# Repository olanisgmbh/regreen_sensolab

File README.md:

# SensoLAB - make, learn and share

The vision of this project is to implement an universal platform which can be used as a citizen science tool and an interdisciplinary tool for schools.

#### the tools You need:

+ screwdrivers
+ solderstation
+ circle cutter
+ punching iron ( 3mm, 8mm )
+ a dremel milling/drilling tool
+ hammer

# Author
Norman Rembarz <norman.rembarz@olanis.de>

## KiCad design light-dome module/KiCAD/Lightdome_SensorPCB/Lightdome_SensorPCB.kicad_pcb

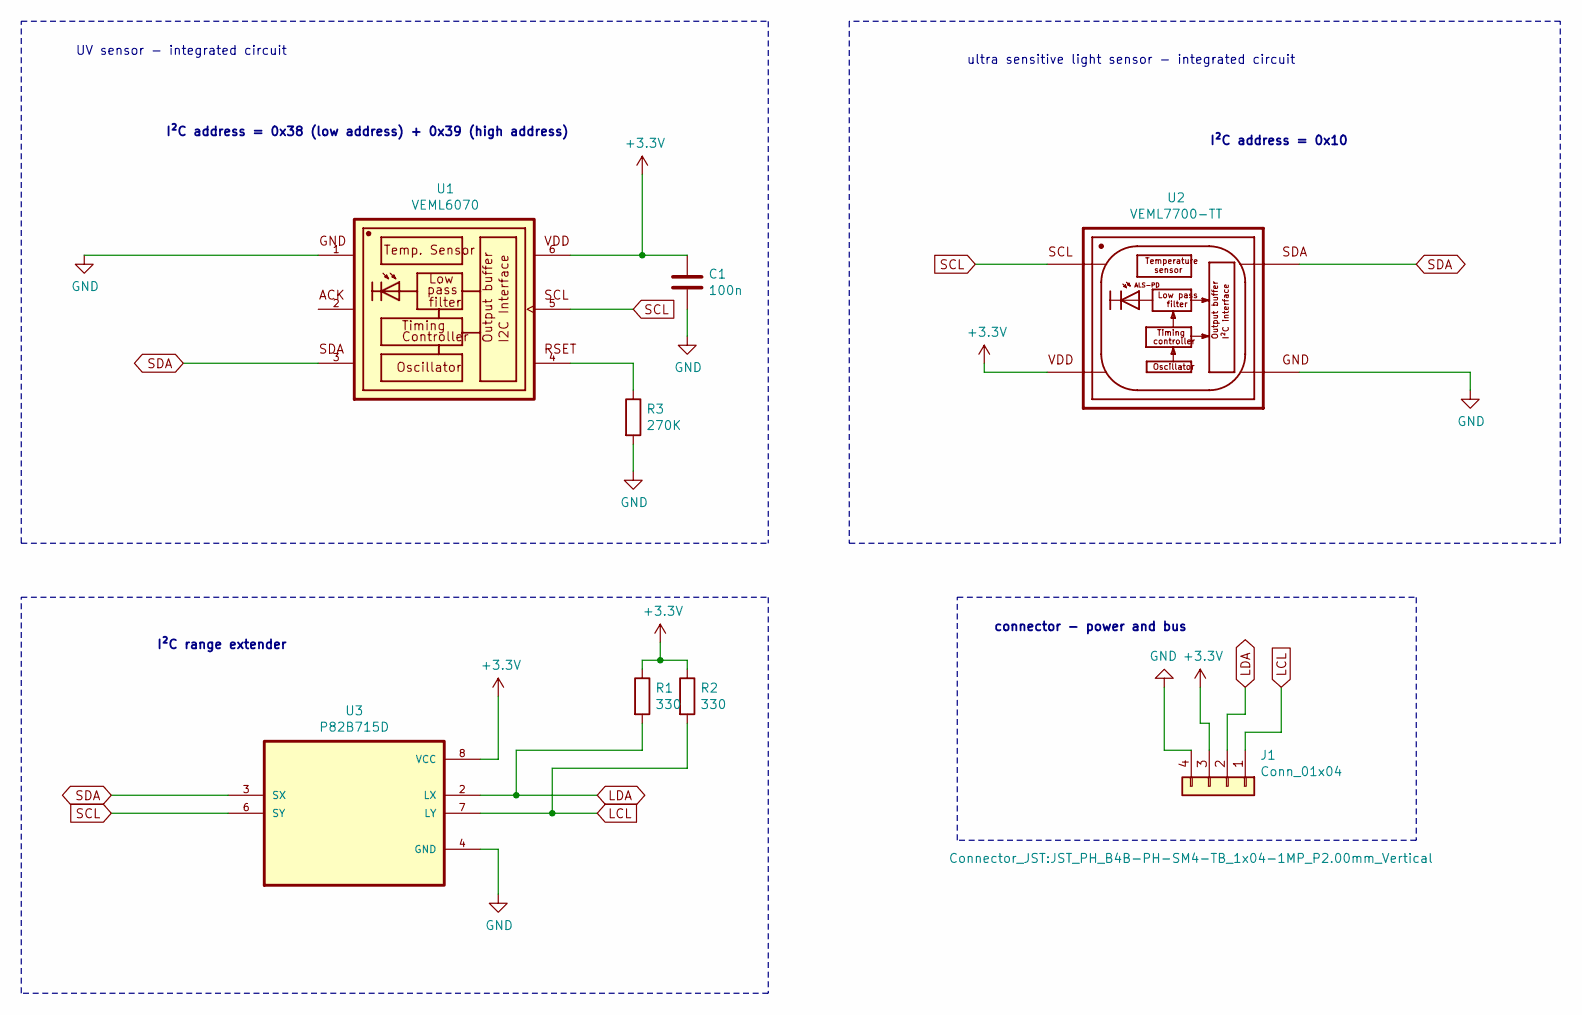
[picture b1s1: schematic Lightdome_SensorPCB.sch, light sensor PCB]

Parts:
C1: 100n; C_0603_1608Metric_Pad1.05x0.95mm_HandSolder
J1: Conn_01x04; JST_PH_B4B-PH-SM4-TB_1x04-1MP_P2.00mm_Vertical
R1, R2: 330; R_1206_3216Metric_Pad1.42x1.75mm_HandSolder
R3: 270K; R_0603_1608Metric_Pad1.05x0.95mm_HandSolder
U1: VEML6070; PHODET_VEML6070
U2: VEML7700-TT; XDCR_VEML7700-TT; PARTREV 1.3
U3: P82B715D; SOIC127P599X175-8N

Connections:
+3V3: C1.1, J1.3, R1.1, R2.1, U1.6, U2.2, U3.8 (VCC)
GND: C1.2, J1.4, R3.2, U1.1, U2.3, U3.4 (GND)
LCL: J1.1, R2.2, U3.7 (LY)
LDA: J1.2, R1.2, U3.2 (LX)
unnamed: R3.1, U1.4
SCL: U1.5, U2.1, U3.6 (SY)
SDA: U1.3, U2.4, U3.3 (SX)

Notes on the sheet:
UV sensor - integrated circuit
ultra sensitive light sensor - integrated circuit
I²C address = 0x10
I²C address = 0x38 (low address) + 0x39 (high address)
I²C range extender
connector - power and bus

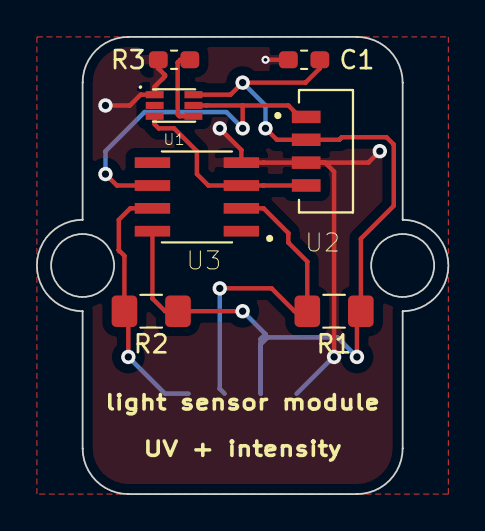
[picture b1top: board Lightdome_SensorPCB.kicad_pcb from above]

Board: 2 copper layers, 22.9 x 25.4 mm, 8 parts (1 on the bottom side), 7 nets.

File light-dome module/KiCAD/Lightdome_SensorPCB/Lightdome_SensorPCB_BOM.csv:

Reference, Value, Footprint, Datasheet, MANUFACTURER, PARTREV, STANDARD
"U1","VEML6070","VEML6070:PHODET_VEML6070","","Vishay","",""
"U2","VEML7700-TT","VEML7700-TT:XDCR_VEML7700-TT","","Vishay","1.3","Manufacturer Recommendation"
"U3","P82B715D","SOIC127P599X175-8N",""
"R1","330","Resistor_SMD:R_1206_3216Metric_Pad1.42x1.75mm_HandSolder","~"
"J1","Conn_01x04","Connector_JST:JST_PH_B4B-PH-SM4-TB_1x04-1MP_P2.00mm_Vertical","~"
"R2","330","Resistor_SMD:R_1206_3216Metric_Pad1.42x1.75mm_HandSolder","~"
"R3","270K","Resistor_SMD:R_0603_1608Metric_Pad1.05x0.95mm_HandSolder","~"
"C1","100n","Capacitor_SMD:C_0603_1608Metric_Pad1.05x0.95mm_HandSolder","~"

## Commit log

2020-10-08 added documentation wind sensor
2020-10-08 addes folder with drawings
2020-11-20 Extended documentation with author
2020-11-20 Not needed anymore
2020-11-20 renamed imagerenamed image
2020-11-20 Update README.md
    text modification
2020-11-20 not needed anymore not needed anymore
2020-11-20 added readme
2020-11-20 not needed for public
2020-11-20 deleted hidden file from MAC OS FS
2020-11-20 modified the intro text
2020-11-24 added some files
2020-11-24 Update README.md
    added image of proto
2020-11-24 added KiCADF project for light sensor PCB
2020-11-24 deleted Sensolab documentation
2020-11-25 added tube drawings
2020-11-25 added README.md for LoRa section
2020-11-27 added BOM
2020-11-27 some changes in bill of material
2020-12-04 changes in light module PCB
2020-12-04 deleted some old files
2020-12-04 added schematic
2020-12-04 changes in BOM
